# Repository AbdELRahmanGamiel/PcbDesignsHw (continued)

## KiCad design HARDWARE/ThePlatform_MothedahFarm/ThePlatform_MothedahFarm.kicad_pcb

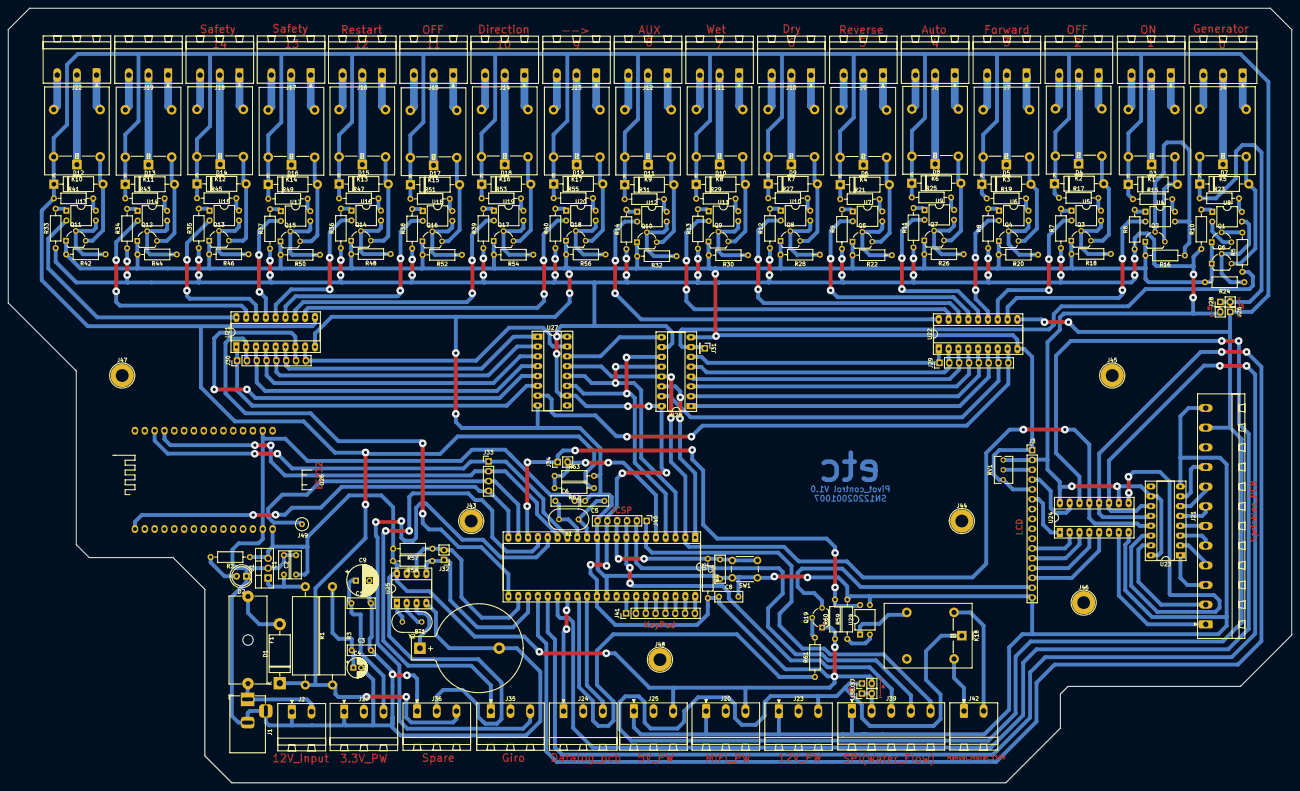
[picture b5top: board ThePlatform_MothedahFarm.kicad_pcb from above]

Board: 2 copper layers, 331.6 x 200.1 mm, 213 parts (1 on the bottom side), 226 nets.

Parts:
BT1: Battery_Cell; BatteryHolder_Keystone_103_1x20mm
C1, C3: 334; C_Disc_D7.0mm_W2.5mm_P5.00mm
C2, C7, C10: 104; C_Disc_D7.0mm_W2.5mm_P5.00mm
C4: 10UF; CP_Radial_D5.0mm_P2.00mm
C5, C6: 22P; C_Disc_D7.0mm_W2.5mm_P5.00mm
C8: 0.1UF; C_Disc_D7.0mm_W2.5mm_P5.00mm
C9: 100UF; CP_Radial_D8.0mm_P3.50mm
D1: 1N5407; D_DO-201AD_P15.24mm_Horizontal
D2: LED; LED_D5.0mm
D3, D4, D5, D6, D7, D8, D9, D10, D11, D12, D13, D14, D15, D16, D17, D18, D19: 1N5407; D_DO-15_P12.70mm_Horizontal
F1: Fuse; Fuseholder_Cylinder-5x20mm_Schurter_0031_8201_Horizontal_Op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
J1: Barrel_Jack_Switch; BarrelJack_Horizontal
J2: 12V_Input; PhoenixContact_MSTBA_2,5_2-G-5,08_1x02_P5.08mm_Horizontal
J3: LCD (20*4); PinHeader_1x16_P2.54mm_Vertical
J4: 0; PhoenixContact_MSTBA_2,5_3-G-5,08_1x03_P5.08mm_Horizontal
J5: 1; PhoenixContact_MSTBA_2,5_3-G-5,08_1x03_P5.08mm_Horizontal
J6: 2; PhoenixContact_MSTBA_2,5_3-G-5,08_1x03_P5.08mm_Horizontal
J7: 3; PhoenixContact_MSTBA_2,5_3-G-5,08_1x03_P5.08mm_Horizontal
J8: 4; PhoenixContact_MSTBA_2,5_3-G-5,08_1x03_P5.08mm_Horizontal
J9: 5; PhoenixContact_MSTBA_2,5_3-G-5,08_1x03_P5.08mm_Horizontal
J10: 6; PhoenixContact_MSTBA_2,5_3-G-5,08_1x03_P5.08mm_Horizontal
J11: 7; PhoenixContact_MSTBA_2,5_3-G-5,08_1x03_P5.08mm_Horizontal
J12: 8; PhoenixContact_MSTBA_2,5_3-G-5,08_1x03_P5.08mm_Horizontal
J13: 9; PhoenixContact_MSTBA_2,5_3-G-5,08_1x03_P5.08mm_Horizontal
J14: 10; PhoenixContact_MSTBA_2,5_3-G-5,08_1x03_P5.08mm_Horizontal
J15: 11; PhoenixContact_MSTBA_2,5_3-G-5,08_1x03_P5.08mm_Horizontal
J16: 12; PhoenixContact_MSTBA_2,5_3-G-5,08_1x03_P5.08mm_Horizontal
J17: 13; PhoenixContact_MSTBA_2,5_3-G-5,08_1x03_P5.08mm_Horizontal
J18: 14; PhoenixContact_MSTBA_2,5_3-G-5,08_1x03_P5.08mm_Horizontal
J19: 15; PhoenixContact_MSTBA_2,5_3-G-5,08_1x03_P5.08mm_Horizontal
J20: MIFI_PW; PhoenixContact_MSTBA_2,5_3-G-5,08_1x03_P5.08mm_Horizontal
J21: INTERFACE for PCB4; PhoenixContact_MSTBA_2,5_12-G-5,08_1x12_P5.08mm_Horizontal
J22: 16; PhoenixContact_MSTBA_2,5_3-G-5,08_1x03_P5.08mm_Horizontal
J23: 12V_PW; PhoenixContact_MSTBA_2,5_3-G-5,08_1x03_P5.08mm_Horizontal
J24: Datalog_pcb; PhoenixContact_MSTBA_2,5_3-G-5,08_1x03_P5.08mm_Horizontal
J25: 5V_PW; PhoenixContact_MSTBA_2,5_3-G-5,08_1x03_P5.08mm_Horizontal
J26, J28, J37, J38: Jumper(V.S); PinHeader_1x02_P2.54mm_Vertical
J27: 3.3V_PW; PhoenixContact_MSTBA_2,5_3-G-5,08_1x03_P5.08mm_Horizontal
J29, J30: RELAYS_OUT; PinHeader_1x08_P2.54mm_Vertical
J31: RELAYS_OUT; PinHeader_1x01_P2.54mm_Vertical
J32: RTC_PinHeaders; PinHeader_1x02_P2.54mm_Vertical
J33: ESP32; PinHeader_1x04_P2.54mm_Vertical
J34: Indicators_PinHeaders; PinHeader_1x02_P2.54mm_Vertical
J35: Giro; PhoenixContact_MSTBA_2,5_3-G-5,08_1x03_P5.08mm_Horizontal
J36: Spare; PhoenixContact_MSTBA_2,5_3-G-5,08_1x03_P5.08mm_Horizontal
J39: SPI(Water_Flow); PhoenixContact_MSTBA_2,5_5-G-5,08_1x05_P5.08mm_Horizontal
J40: SPI(ISP); PinHeader_1x06_P2.54mm_Vertical
J41: Keypad; PinHeader_1x08_P2.54mm_Vertical
J42: Manual_Indcat_110V; PhoenixContact_MSTBA_2,5_2-G-5,08_1x02_P5.08mm_Horizontal
J43: 1; TestPoint_Plated_Hole_D5.0mm
J44: 4; TestPoint_Plated_Hole_D5.0mm
J45: 2; TestPoint_Plated_Hole_D5.0mm
J46: 5; TestPoint_Plated_Hole_D5.0mm
J47: 3; TestPoint_Plated_Hole_D5.0mm
J48: 6; TestPoint_Plated_Hole_D5.0mm
J49: BOOT_Pad; TestPoint_Loop_D2.54mm_Drill1.5mm_Beaded
K1, K2, K3, K4, K5, K6, K7, K8, K9, K10, K11, K12, K13, K14, K15, K16, K17, K18: G5LE-1; Relay_SPDT_Omron-G5LE-1
Q1, Q2, Q3, Q4, Q5, Q6, Q7, Q8, Q9, Q10, Q11, Q12, Q13, Q14, Q15, Q16, Q17, Q18: 2N2219; TO-92L_Wide
Q19: 2N3906; TO-92L_Wide
R1: 10/2W; R_Axial_Power_L20.0mm_W6.4mm_P25.40mm
R2: 330; R_Axial_DIN0207_L6.3mm_D2.5mm_P10.16mm_Horizontal
R3: 10/3W; R_Axial_Power_L20.0mm_W6.4mm_P25.40mm
R4, R57, R58, R60, R62: 10K; R_Axial_DIN0207_L6.3mm_D2.5mm_P10.16mm_Horizontal
R5, R16, R18, R20, R22, R24, R26, R28, R30, R32, R42, R44, R46, R48, R50, R52, R54, R56: 1K; R_Axial_DIN0207_L6.3mm_D2.5mm_P10.16mm_Horizontal
R6, R7, R8, R9, R10, R11, R12, R13, R14, R33, R34, R35, R36, R37, R38, R39, R40: 150; R_Axial_DIN0207_L6.3mm_D2.5mm_P10.16mm_Horizontal
R15, R17, R19, R21, R23, R25, R27, R29, R31, R41, R43, R45, R47, R49, R51, R53, R55: 1900; R_Axial_DIN0207_L6.3mm_D2.5mm_P10.16mm_Horizontal
R59: 500; R_Axial_DIN0207_L6.3mm_D2.5mm_P10.16mm_Horizontal
R61, R63: 5K; R_Axial_DIN0207_L6.3mm_D2.5mm_P10.16mm_Horizontal
RV1: R_POT; Potentiometer_Bourns_3266Y_Vertical
SW1: SW_Push; SW_PUSH_6mm_H7.3mm
U1: L7805; TO-220-3_Vertical
U2: AMS1117-3.3; SOT-223-3_TabPin2
U3: ATmega32-16PU; DIP-40_W15.24mm_Socket_LongPads
U4, U5, U6, U7, U8, U9, U10, U11, U12, U13, U14, U15, U16, U17, U18, U19, U20, U29: EL817; DIP-4_W7.62mm
U21, U22: ULN2803A; DIP-18_W7.62mm_Socket_LongPads
U23, U24, U27, U28: 74AHCT595; DIP-16_W7.62mm_Socket_LongPads
U25: DS1307+; DIP-8_W7.62mm_Socket_LongPads
U26: ESP32_module
Y1: 16MH; Resonator-2Pin_W10.0mm_H5.0mm
Y2: Crystal; Resonator-2Pin_W10.0mm_H5.0mm

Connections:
/3.3V: C9.1, C10.1, J27.3, U2.2
/5V: C2.1, C8.1, J3.2, J20.3, J25.3, J26.2, J36.2, J37.2, J40.5, Q19.1, R2.1, R4.2, R6.1, R7.1, R8.1, R9.1, R10.1, R11.1, R12.1, R13.1, R14.1, R33.1, R34.1, R35.1, R36.1, R37.1, R38.1, R39.1, R40.1, R57.2, R58.2, R60.1, RV1.1, U1.3, U3.10, U3.30, U23.10, U23.16, U24.10, U24.16, U25.8, U26.16, U27.10, U27.16, U28.10, U28.16
/12V: D1.1, D3.1, D4.1, D5.1, D6.1, D8.1, D9.1, D10.1, D11.1, D12.1, D13.1, D14.1, D15.1, D16.1, D17.1, D18.1, D19.1, J21.11, J23.3, J26.1, J36.3, J37.1, K1.5, K2.5, K3.5, K4.5, K6.5, K7.5, K8.5, K9.5, K10.5, K11.5, K12.5, K13.5, K14.5, K15.5, K16.5, K17.5, K18.1, R1.2, R3.2, R15.1, R17.1, R19.1, R21.1, R25.1, R27.1, R29.1, R31.1, R41.1, R43.1, R45.1, R47.1, R49.1, R51.1, R53.1, R55.1, R62.1, U21.10, U22.10
/110V: J42.1, K18.5
/BOOT: J33.3, J49.1, U3.19
/COL1: J41.5, U3.37
/COL2: J41.6, U3.38
/COL3: J41.7, U3.39
/COL4: J41.8, U3.40
/COM0: J4.2, K5.1
/COM1: J5.2, K1.1
/COM2: J6.2, K2.1
/COM3: J7.2, K3.1
/COM4: J8.2, K6.1
/COM5: J9.2, K4.1
/COM6: J10.2, K7.1
/COM7: J11.2, K8.1
/COM8: J12.2, K9.1
/COM9: J13.2, K17.1
/COM10: J14.2, K16.1
/COM11: J15.2, K15.1
/COM12: J16.2, K13.1
/COM13: J17.2, K14.1
/COM14: J18.2, K12.1
/COM15: J19.2, K11.1
/COM16: J22.2, K10.1
/DB4: J3.11, U24.2
/DB5: J3.12, U24.3
/DB6: J3.13, U24.4
/DB7: J3.14, U24.5
/E: J3.6, U24.1
/EN_BKL: R61.1, U3.28
/EN_ESP32: J33.4, U3.20, U26.30
/EN_SR: U3.2, U23.13, U24.13, U27.13, U28.13
/GND: BT1.2, C1.2, C2.2, C3.2, C4.2, C5.2, C6.2, C7.1, C8.2, C9.2, C10.2, D2.1, J1.2, J1.3, J2.1, J3.1, J3.5, J3.16, J20.1, J21.12, J23.1, J25.1, J27.1, J36.1, J39.1, J40.6, Q1.1, Q2.1, Q3.1, Q4.1, Q5.1, Q6.1, Q7.1, Q8.1, Q9.1, Q10.1, Q11.1, Q12.1, Q13.1, Q14.1, Q15.1, Q16.1, Q17.1, Q18.1, R16.2, R18.2, R20.2, R22.2, R24.2, R26.2, R28.2, R30.2, R32.2, R42.2, R44.2, R46.2, R48.2, R50.2, R52.2, R54.2, R56.2, R59.2, R63.2, RV1.3, SW1.1, U1.2, U2.1, U3.11, U3.31, U21.9, U22.9, U23.8, U24.8, U25.4, U26.2, U26.17, U27.8, U28.8, U29.3
/Generator_Indicator: J34.2, R62.2, R63.1, U3.5
/JUM: D7.1, J28.1, J28.2, K5.5, R23.1
/LCD_BKL: J3.15, Q19.3
/MISO: J39.4, J40.2, U3.7
/MOSI: J39.5, J40.1, U3.6
/Manual_Indicator: J34.1, R60.2, U3.18, U29.4
/N: J42.2, K18.2
/NC0: J4.3, K5.4
/NC1: J5.3, K1.4
/NC2: J6.3, K2.4
/NC3: J7.3, K3.4
/NC4: J8.3, K6.4
/NC5: J9.3, K4.4
/NC6: J10.3, K7.4
/NC7: J11.3, K8.4
/NC8: J12.3, K9.4
/NC9: J13.3, K17.4
/NC10: J14.3, K16.4
/NC11: J15.3, K15.4
/NC12: J16.3, K13.4
/NC13: J17.3, K14.4
/NC14: J18.3, K12.4
/NC15: J19.3, K11.4
/NC16: J22.3, K10.4
/NO0: J4.1, K5.3
/NO1: J5.1, K1.3
/NO2: J6.1, K2.3
/NO3: J7.1, K3.3
/NO4: J8.1, K6.3
/NO5: J9.1, K4.3
/NO6: J10.1, K7.3
/NO7: J11.1, K8.3
/NO8: J12.1, K9.3
/NO9: J13.1, K17.3
/NO10: J14.1, K16.3
/NO11: J15.1, K15.3
/NO12: J16.1, K13.3
/NO13: J17.1, K14.3
/NO14: J18.1, K12.3
/NO15: J19.1, K11.3
/NO16: J22.1, K10.3
/RCLK: U3.24, U23.12, U24.12
/RCLK_RELAYS: U3.3, U27.12, U28.12
/REL_0: J31.1, R5.1, U28.7
/REL_1: J29.8, U22.8, U27.7
/REL_2: J29.7, U22.7, U28.15
/REL_3: J29.6, U22.6, U28.1
/REL_4: J29.5, U22.5, U28.2
/REL_5: J29.4, U22.4, U28.3
/REL_6: J29.3, U22.3, U28.4
/REL_7: J29.2, U22.2, U28.5
/REL_8: J29.1, U22.1, U28.6
/REL_9: J30.8, U21.8, U27.15
/REL_10: J30.7, U21.7, U27.5
/REL_11: J30.6, U21.6, U27.1
/REL_12: J30.5, U21.5, U27.2
/REL_13: J30.4, U21.4, U27.3
/REL_14: J30.3, U21.3, U27.4
/REL_15: J30.2, U3.21, U21.2
/REL_16: J30.1, U21.1, U27.6
/REL_17: J21.1, U24.7
/REL_18: J21.2, U23.15
/REL_19: J21.3, U23.1
/REL_20: J21.4, U23.2
/REL_21: J21.5, U23.3
/REL_22: J21.6, U23.4
/REL_23: J21.7, U23.5
/REL_24: J21.8, U23.6
/REL_25: J21.9, U23.7
/REL_UL_1: U4.2, U22.11
/REL_UL_2: U5.2, U22.12
/REL_UL_3: U6.2, U22.13
/REL_UL_4: U9.2, U22.14
/REL_UL_5: U7.2, U22.15
/REL_UL_6: U10.2, U22.16
/REL_UL_7: U11.2, U22.17
/REL_UL_8: U12.2, U22.18
/REL_UL_9: U20.2, U21.11
/REL_UL_10: U19.2, U21.12
/REL_UL_11: U18.2, U21.13
/REL_UL_12: U16.2, U21.14
/REL_UL_13: U17.2, U21.15
/REL_UL_14: U15.2, U21.16
/REL_UL_15: U14.2, U21.17
/REL_UL_16: U13.2, U21.18
/ROW1: J41.1, U3.33
/ROW2: J41.2, U3.34
/ROW3: J41.3, U3.35
/ROW4: J41.4, U3.36
/RS: J3.4, U24.15
/RST: C7.2, J40.4, R4.1, SW1.2, U3.9
/RTC_SCL: J32.2, R57.1, U3.22, U25.6
/RTC_SDA: J32.1, R58.1, U3.23, U25.5
/RX-MCU: J33.1, U3.14, U26.13
/RX_Giro: J35.1, U3.17
/RX_logger: J24.3, U3.29
/SCK: J39.3, J40.3, U3.8
/SCK_RELAYS: U3.4, U27.11, U28.11
/SER: U3.26, U24.14
/SER_RELAYS: U3.1, U28.14
/SRCLK: U3.25, U23.11, U24.11
/TX_Giro: J35.3, U3.16
/TX_MCU: J33.2, U3.15, U26.12
/TX_logger: J24.1, U3.27
/VO: J3.3, RV1.2
/jum: J38.1, J38.2, J39.2
unnamed: BT1.1, U25.3
unnamed: C1.1, R1.1, U1.1
unnamed: C3.1, C4.1, R3.1, U2.3
unnamed: C5.1, U3.12, Y1.1
unnamed: C6.1, U3.13, Y1.2
unnamed: D1.2, F1.1
unnamed: D2.2, R2.2
unnamed: D3.2, K1.2, Q2.3
unnamed: D4.2, K2.2, Q3.3
unnamed: D5.2, K3.2, Q4.3
unnamed: D6.2, K4.2, Q5.3
unnamed: D7.2, K5.2, Q6.3
unnamed: D8.2, K6.2, Q7.3
unnamed: D9.2, K7.2, Q8.3
unnamed: D10.2, K8.2, Q9.3
unnamed: D11.2, K9.2, Q10.3
unnamed: D12.2, K10.2, Q11.3
unnamed: D13.2, K11.2, Q12.3
unnamed: D14.2, K12.2, Q13.3
unnamed: D15.2, K13.2, Q14.3
unnamed: D16.2, K14.2, Q15.3
unnamed: D17.2, K15.2, Q16.3
unnamed: D18.2, K16.2, Q17.3
unnamed: D19.2, K17.2, Q18.3
unnamed: F1.2, J1.1, J2.2
unnamed: K18.3, U29.1
unnamed: Q1.2, R5.2
unnamed: Q1.3, U8.2
unnamed: Q2.2, R16.1, U4.3
unnamed: Q3.2, R18.1, U5.3
unnamed: Q4.2, R20.1, U6.3
unnamed: Q5.2, R22.1, U7.3
unnamed: Q6.2, R24.1, U8.3
unnamed: Q7.2, R26.1, U9.3
unnamed: Q8.2, R28.1, U10.3
unnamed: Q9.2, R30.1, U11.3
unnamed: Q10.2, R32.1, U12.3
unnamed: Q11.2, R42.1, U13.3
unnamed: Q12.2, R44.1, U14.3
unnamed: Q13.2, R46.1, U15.3
unnamed: Q14.2, R48.1, U16.3
unnamed: Q15.2, R50.1, U17.3
unnamed: Q16.2, R52.1, U18.3
unnamed: Q17.2, R54.1, U19.3
unnamed: Q18.2, R56.1, U20.3
unnamed: Q19.2, R61.2
unnamed: R6.2, U4.1
unnamed: R7.2, U5.1
unnamed: R8.2, U6.1
unnamed: R9.2, U7.1
unnamed: R10.2, U8.1
unnamed: R11.2, U9.1
unnamed: R12.2, U10.1
unnamed: R13.2, U11.1
unnamed: R14.2, U12.1
unnamed: R15.2, U4.4
unnamed: R17.2, U5.4
unnamed: R19.2, U6.4
unnamed: R21.2, U7.4
unnamed: R23.2, U8.4
unnamed: R25.2, U9.4
unnamed: R27.2, U10.4
unnamed: R29.2, U11.4
unnamed: R31.2, U12.4
unnamed: R33.2, U13.1
unnamed: R34.2, U14.1
unnamed: R35.2, U15.1
unnamed: R36.2, U16.1
unnamed: R37.2, U17.1
unnamed: R38.2, U18.1
unnamed: R39.2, U19.1
unnamed: R40.2, U20.1
unnamed: R41.2, U13.4
unnamed: R43.2, U14.4
unnamed: R45.2, U15.4
unnamed: R47.2, U16.4
unnamed: R49.2, U17.4
unnamed: R51.2, U18.4
unnamed: R53.2, U19.4
unnamed: R55.2, U20.4
unnamed: R59.1, U29.2
unnamed: U23.14, U24.9
unnamed: U25.1, Y2.2
unnamed: U25.2, Y2.1
unnamed: U27.14, U28.9

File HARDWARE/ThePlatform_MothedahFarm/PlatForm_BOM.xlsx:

no | References | Value | Footprint | Quantity
1 | C4 | 10UF | CP_Radial_D5.0mm_P2.00mm | 1
2 | C9 | 100UF | CP_Radial_D8.0mm_P3.50mm | 1
3 | C2, C7, C10 | 104 | C_Disc_D7.0mm_W2.5mm_P5.00mm | 3
4 | C1, C3 | 334 | C_Disc_D7.0mm_W2.5mm_P5.00mm | 2
5 | C5, C6 | 22P | C_Disc_D7.0mm_W2.5mm_P5.00mm | 2
6 | C8 | 0.1UF | C_Disc_D7.0mm_W2.5mm_P5.00mm | 1
7 | R5, R16, R18, R20, R22, R24, R26, R28, R30, R32, R42, R44, R46, R48, R50, R52, 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 | 1K | R_Axial_DIN0207_L6.3mm_D2.5mm_P10.16mm_Horizontal | 18
8 | R6, R7, R8, R9, R10, R11, R12, R13, R14, R33, R34, R35, R36, R37, R38, R39, R40 | 150 | R_Axial_DIN0207_L6.3mm_D2.5mm_P10.16mm_Horizontal | 17
9 | R15, R17, R19, R21, R23, R25, R27, R29, R31, R41, R43, R45, R47, R49, R51, R53,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 | 1900 | R_Axial_DIN0207_L6.3mm_D2.5mm_P10.16mm_Horizontal | 17
10 | R4, R57, R58, R60, R62 | 10K | R_Axial_DIN0207_L6.3mm_D2.5mm_P10.16mm_Horizontal | 5
11 | R61, R63 | 5K | R_Axial_DIN0207_L6.3mm_D2.5mm_P10.16mm_Horizontal | 2
12 | R2 | 330 | R_Axial_DIN0207_L6.3mm_D2.5mm_P10.16mm_Horizontal | 1
13 | R59 | 500 | R_Axial_DIN0207_L6.3mm_D2.5mm_P10.16mm_Horizontal | 1
14 | R1 | 10/2W | R_Axial_Power_L20.0mm_W6.4mm_P25.40mm | 1
15 | R3 | 10/3W | R_Axial_Power_L20.0mm_W6.4mm_P25.40mm | 1
16 | D3, D4, D5, D6, D7, D8, D9, D10, D11, D12, D13, D14, D15, D16, D17, D18, D19 | 1N5407 | D_DO-15_P12.70mm_Horizontal | 17
17 | D1 | 1N5407 | D_DO-201AD_P15.24mm_Horizontal | 1
18 | D2 | LED | LED_D5.0mm | 1
19 | U23, U24, U27, U28 | 74AHCT595 | DIP-16_W7.62mm_Socket_LongPads | 4
20 | U21, U22 | ULN2803A | DIP-18_W7.62mm_Socket_LongPads | 2
21 | U3 | ATmega32-16PU | DIP-40_W15.24mm_Socket_LongPads | 1
22 | U4, U5, U6, U7, U8, U9, U10, U11, U12, U13, U14, U15, U16, U17, U18, U19, U20, 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 | EL817 | DIP-4_W7.62mm | 18
23 | U25 | DS1307+ | DIP-8_W7.62mm_Socket_LongPads | 1
24 | U26 | ESP32_module | ESP32_module | 1
25 | U2 | AMS1117-3.3 | SOT-223-3_TabPin2 | 1
26 | U1 | L7805 | TO-220-3_Vertical | 1
27 | Y1 | 16MH | Resonator-2Pin_W10.0mm_H5.0mm | 1
28 | Y2 | Crystal | Resonator-2Pin_W10.0mm_H5.0mm | 1
29 | F1 | Fuse | Fuseholder_Cylinder-5x20mm_Schurter_0031_8201_Horizontal_Open | 1
30 | SW1 | SW_Push | SW_PUSH_6mm_H7.3mm | 1
31 | BT1 | Battery_Cell | BatteryHolder_Keystone_103_1x20mm | 1
32 | RV1 | R_POT | Potentiometer_Bourns_3266Y_Vertical | 1
33 | K1, K2, K3, K4, K5, K6, K7, K8, K9, K10, K11, K12, K13, K14, K15, K16, K17, K18 | G5LE-1 | Relay_SPDT_Omron-G5LE-1 | 18
34 | Q1, Q2, Q3, Q4, Q5, Q6, Q7, Q8, Q9, Q10, Q11, Q12, Q13, Q14, Q15, Q16, Q17, Q18 | 2N2219 | TO-92L_Wide | 18
35 | Q19 | 2N3906 | TO-92L_Wide | 1
36 | J1 | Barrel_Jack_Switch | BarrelJack_Horizontal | 1
37 | J21 | INTERFACE for PCB4 | PhoenixContact_MSTBA_2,5_12-G-5,08_1x12_P5.08mm_Horizontal | 1
38 | J2 | 12V_Input | PhoenixContact_MSTBA_2,5_2-G-5,08_1x02_P5.08mm_Horizontal | 1
39 | J42 | Manual_Indcat_110V | PhoenixContact_MSTBA_2,5_2-G-5,08_1x02_P5.08mm_Horizontal | 1
40 | J4 | 0 | PhoenixContact_MSTBA_2,5_3-G-5,08_1x03_P5.08mm_Horizontal | 1
41 | J5 | 1 | PhoenixContact_MSTBA_2,5_3-G-5,08_1x03_P5.08mm_Horizontal | 1
42 | J6 | 2 | PhoenixContact_MSTBA_2,5_3-G-5,08_1x03_P5.08mm_Horizontal | 1
43 | J7 | 3 | PhoenixContact_MSTBA_2,5_3-G-5,08_1x03_P5.08mm_Horizontal | 1
44 | J8 | 4 | PhoenixContact_MSTBA_2,5_3-G-5,08_1x03_P5.08mm_Horizontal | 1
45 | J9 | 5 | PhoenixContact_MSTBA_2,5_3-G-5,08_1x03_P5.08mm_Horizontal | 1
46 | J10 | 6 | PhoenixContact_MSTBA_2,5_3-G-5,08_1x03_P5.08mm_Horizontal | 1
47 | J11 | 7 | PhoenixContact_MSTBA_2,5_3-G-5,08_1x03_P5.08mm_Horizontal | 1
48 | J12 | 8 | PhoenixContact_MSTBA_2,5_3-G-5,08_1x03_P5.08mm_Horizontal | 1
49 | J13 | 9 | PhoenixContact_MSTBA_2,5_3-G-5,08_1x03_P5.08mm_Horizontal | 1
50 | J14 | 10 | PhoenixContact_MSTBA_2,5_3-G-5,08_1x03_P5.08mm_Horizontal | 1
51 | J15 | 11 | PhoenixContact_MSTBA_2,5_3-G-5,08_1x03_P5.08mm_Horizontal | 1
52 | J16 | 12 | PhoenixContact_MSTBA_2,5_3-G-5,08_1x03_P5.08mm_Horizontal | 1
53 | J17 | 13 | PhoenixContact_MSTBA_2,5_3-G-5,08_1x03_P5.08mm_Horizontal | 1
54 | J18 | 14 | PhoenixContact_MSTBA_2,5_3-G-5,08_1x03_P5.08mm_Horizontal | 1
55 | J19 | 15 | PhoenixContact_MSTBA_2,5_3-G-5,08_1x03_P5.08mm_Horizontal | 1
56 | J20 | MIFI_PW | PhoenixContact_MSTBA_2,5_3-G-5,08_1x03_P5.08mm_Horizontal | 1
57 | J22 | 16 | PhoenixContact_MSTBA_2,5_3-G-5,08_1x03_P5.08mm_Horizontal | 1
58 | J23 | 12V_PW | PhoenixContact_MSTBA_2,5_3-G-5,08_1x03_P5.08mm_Horizontal | 1
59 | J24 | Datalog_pcb | PhoenixContact_MSTBA_2,5_3-G-5,08_1x03_P5.08mm_Horizontal | 1
60 | J25 | 5V_PW | PhoenixContact_MSTBA_2,5_3-G-5,08_1x03_P5.08mm_Horizontal | 1
61 | J27 | 3.3V_PW | PhoenixContact_MSTBA_2,5_3-G-5,08_1x03_P5.08mm_Horizontal | 1
62 | J35 | Giro | PhoenixContact_MSTBA_2,5_3-G-5,08_1x03_P5.08mm_Horizontal | 1
63 | J36 | Spare | PhoenixContact_MSTBA_2,5_3-G-5,08_1x03_P5.08mm_Horizontal | 1
64 | J39 | SPI(Water_Flow) | PhoenixContact_MSTBA_2,5_5-G-5,08_1x05_P5.08mm_Horizontal | 1
65 | J31 | RELAYS_OUT | PinHeader_1x01_P2.54mm_Vertical | 1
66 | J26, J28, J37, J38 | Jumper(V.S) | PinHeader_1x02_P2.54mm_Vertical | 4
67 | J32 | RTC_PinHeaders | PinHeader_1x02_P2.54mm_Vertical | 1
68 | J34 | Indicators_PinHeaders | PinHeader_1x02_P2.54mm_Vertical | 1
69 | J33 | ESP32 | PinHeader_1x04_P2.54mm_Vertical | 1
70 | J40 | SPI(ISP) | PinHeader_1x06_P2.54mm_Vertical | 1
71 | J29, J30 | RELAYS_OUT | PinHeader_1x08_P2.54mm_Vertical | 2
72 | J41 | Keypad | PinHeader_1x08_P2.54mm_Vertical | 1
73 | J3 | LCD (20*4) | PinHeader_1x16_P2.54mm_Vertical | 1
74 | J49 | BOOT_Pad | TestPoint_Loop_D2.54mm_Drill1.5mm_Beaded | 1
75 |  | MOSFET | IRF634 | 10

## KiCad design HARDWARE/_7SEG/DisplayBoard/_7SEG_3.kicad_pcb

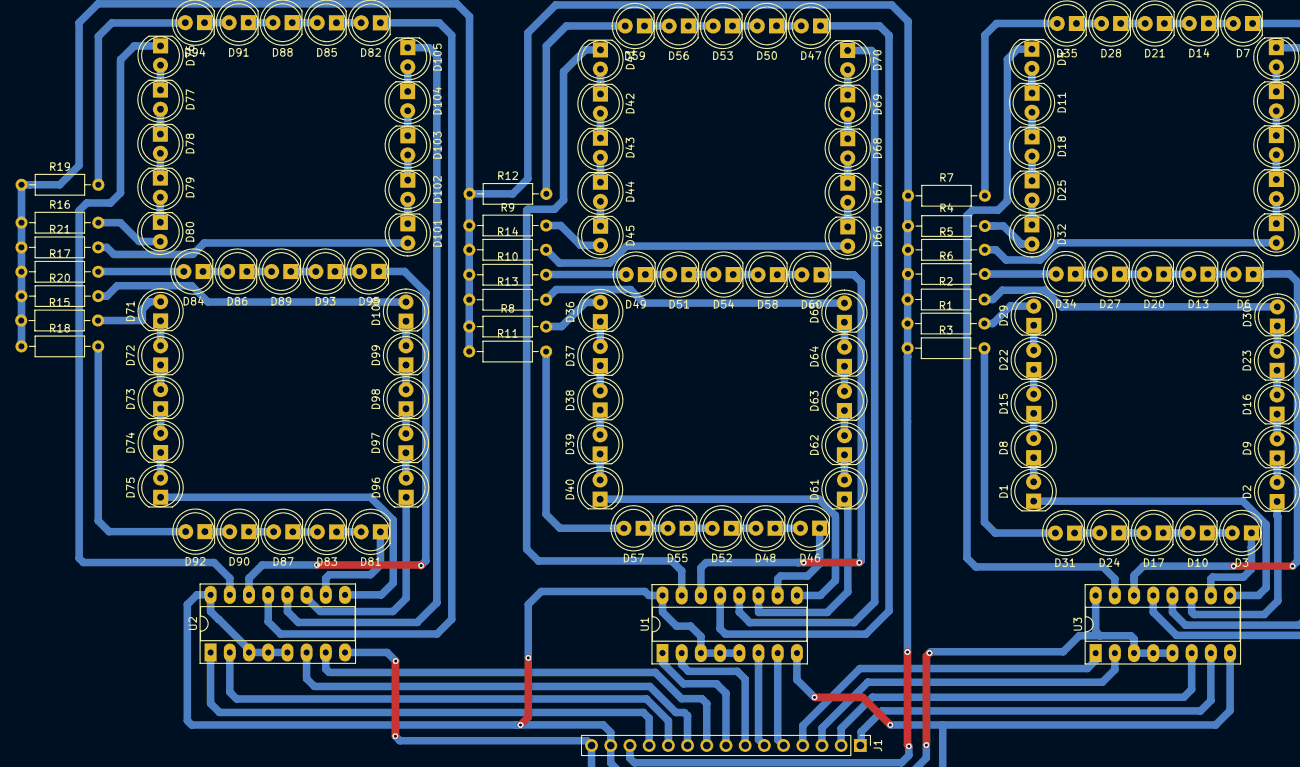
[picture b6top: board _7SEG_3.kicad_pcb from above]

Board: 2 copper layers, 130 parts (0 on the bottom side), 141 nets.

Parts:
D1, D2, D3, D4, D5, D6, D7, D8, D9, D10, D11, D12, D13, D14, D15, D16, D17, D18, D19, D20, D21, D22, D23, D24, D25, D26, D27, D28, D29, D30, D31, D32, D33, D34, D35, D36, D37, D38, D39, D40, D41, D42, D43, D44, D45, D46, D47, D48, D49, D50, D51, D52, D53, D54, D55, D56, D57, D58, D59, D60, D61, D62, D63, D64, D65, D66, D67, D68, D69, D70, D71, D72, D73, D74, D75, D76, D77, D78, D79, D80, D81, D82, D83, D84, D85, D86, D87, D88, D89, D90, D91, D92, D93, D94, D95, D96, D97, D98, D99, D100, D101, D102, D103, D104, D105: LED; LED_D5.0mm
J1: Conn_01x15_Female; PinHeader_1x15_P2.54mm_Vertical
R1, R2, R3, R4, R5, R6, R7, R8, R9, R10, R11, R12, R13, R14, R15, R16, R17, R18, R19, R20, R21: R; R_Axial_DIN0207_L6.3mm_D2.5mm_P10.16mm_Horizontal
U1, U2, U3: 74LS47; DIP-16_W7.62mm_Socket_LongPads

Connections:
/A_D1: J1.1, U3.7
/A_D2: J1.5, U1.7
/A_D3: J1.9, U2.7
/B_D1: J1.4, U3.1
/B_D2: J1.8, U1.1
/B_D3: J1.12, U2.1
/C_D1: J1.3, U3.2
/C_D2: J1.7, U1.2
/C_D3: J1.11, U2.2
/D_D1: J1.2, U3.6
/D_D2: J1.6, U1.6
/D_D3: J1.10, U2.6
/a_1: D7.1, U3.13
/a_2: D47.1, U1.13
/a_3: D82.1, U2.13
/b_1: D5.1, U3.12
/b_2: D70.1, U1.12
/b_3: D105.1, U2.12
/c_1: D2.1, U3.11
/c_2: D61.1, U1.11
/c_3: D96.1, U2.11
/d_1: D3.1, U3.10
/d_2: D46.1, U1.10
/d_3: D81.1, U2.10
/e_1: D1.1, U3.9
/e_2: D40.1, U1.9
/e_3: D75.1, U2.9
/f_1: D4.1, U3.15
/f_2: D41.1, U1.15
/f_3: D76.1, U2.15
/g_1: D6.1, U3.14
/g_2: D60.1, U1.14
/g_3: D95.1, U2.14
GND: J1.15, U1.8, U2.8, U3.8
unnamed: D1.2, D8.1
unnamed: D2.2, D9.1
unnamed: D3.2, D10.1
unnamed: D10.2, D17.1
unnamed: D4.2, D11.1
unnamed: D11.2, D18.1
unnamed: D5.2, D12.1
unnamed: D12.2, D19.1
unnamed: D6.2, D13.1
unnamed: D13.2, D20.1
unnamed: D7.2, D14.1
unnamed: D14.2, D21.1
unnamed: D8.2, D15.1
unnamed: D15.2, D22.1
unnamed: D9.2, D16.1
unnamed: D16.2, D23.1
unnamed: D17.2, D24.1
unnamed: D18.2, D25.1
unnamed: D19.2, D26.1
unnamed: D20.2, D27.1
unnamed: D21.2, D28.1
unnamed: D22.2, D29.1
unnamed: D23.2, D30.1
unnamed: D24.2, D31.1
unnamed: D25.2, D32.1
unnamed: D26.2, D33.1
unnamed: D27.2, D34.1
unnamed: D28.2, D35.1
unnamed: D29.2, R1.2
unnamed: D30.2, R2.2
unnamed: D31.2, R3.2
unnamed: D32.2, R4.2
unnamed: D33.2, R5.2
unnamed: D34.2, R6.2
unnamed: D35.2, R7.2
unnamed: D36.1, D37.2
unnamed: D36.2, R8.2
unnamed: D37.1, D38.2
unnamed: D38.1, D39.2
unnamed: D39.1, D40.2
unnamed: D41.2, D42.1
unnamed: D42.2, D43.1
unnamed: D43.2, D44.1
unnamed: D44.2, D45.1
unnamed: D45.2, R9.2
unnamed: D46.2, D48.1
unnamed: D47.2, D50.1
unnamed: D48.2, D52.1
unnamed: D49.1, D51.2
unnamed: D49.2, R10.2
unnamed: D50.2, D53.1
unnamed: D51.1, D54.2
unnamed: D52.2, D55.1
unnamed: D53.2, D56.1
unnamed: D54.1, D58.2
unnamed: D55.2, D57.1
unnamed: D56.2, D59.1
unnamed: D57.2, R11.2
unnamed: D58.1, D60.2
unnamed: D59.2, R12.2
unnamed: D61.2, D62.1
unnamed: D62.2, D63.1
unnamed: D63.2, D64.1
unnamed: D64.2, D65.1
unnamed: D65.2, R13.2
unnamed: D66.1, D67.2
unnamed: D66.2, R14.2
unnamed: D67.1, D68.2
unnamed: D68.1, D69.2
unnamed: D69.1, D70.2
unnamed: D71.1, D72.2
unnamed: D71.2, R15.2
unnamed: D72.1, D73.2
unnamed: D73.1, D74.2
unnamed: D74.1, D75.2
unnamed: D76.2, D77.1
unnamed: D77.2, D78.1
unnamed: D78.2, D79.1
unnamed: D79.2, D80.1
unnamed: D80.2, R16.2
unnamed: D81.2, D83.1
unnamed: D82.2, D85.1
unnamed: D83.2, D87.1
unnamed: D84.1, D86.2
unnamed: D84.2, R17.2
unnamed: D85.2, D88.1
unnamed: D86.1, D89.2
unnamed: D87.2, D90.1
unnamed: D88.2, D91.1
unnamed: D89.1, D93.2
unnamed: D90.2, D92.1
unnamed: D91.2, D94.1
unnamed: D92.2, R18.2
unnamed: D93.1, D95.2
unnamed: D94.2, R19.2
unnamed: D96.2, D97.1
unnamed: D97.2, D98.1
unnamed: D98.2, D99.1
unnamed: D99.2, D100.1
unnamed: D100.2, R20.2
unnamed: D101.1, D102.2
unnamed: D101.2, R21.2
unnamed: D102.1, D103.2
unnamed: D103.1, D104.2
unnamed: D104.1, D105.2
VCC: J1.14, U1.3, U1.4, U1.5, U1.16, U2.3, U2.4, U2.5, U2.16, U3.3, U3.4, U3.5, U3.16
VDD: J1.13, R1.1, R2.1, R3.1, R4.1, R5.1, R6.1, R7.1, R8.1, R9.1, R10.1, R11.1, R12.1, R13.1, R14.1, R15.1, R16.1, R17.1, R18.1, R19.1, R20.1, R21.1
